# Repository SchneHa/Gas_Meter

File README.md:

# Gasverbrauch messen und verarbeiten 

## Funktion

Manche Gaszähler geben pro verbrauchte 10 Liter einen magnetischen Impuls ab.
Dieser Impuls wird mit einem Hall Sensor in elektrische Impulse umgewandelt, ein RTC Baustein PCF8583 arbeitet als Zähler und speichert die Zahl der Impulse im internen RAM ab.

PCB Eagle Dateien (für Version 1.3) und KiCAD Dateien (für Version 1.4) sowie Stückliste (BOM) für beide Versionen anbei.

Ich habe sowohl für die Version 1.3 als auch für die Version 1.4 noch einige Platinen übrig, bei Bedarf bitte melden:
```
PCB unbestückt: 5€
PCB mit Bauteilen: 15€
PCB fertig bestückt (ohne Knopfzelle und Hallsensor noch nicht bestückt): 20€
D1 mini ESP8266: 10€
inklusive Versand innerhalb Deutschlands
hans(dot)schneider(at)gmx(dot)ch
```

Die Daten werden mit Hilfe eines ESP8266 (z.B. Wemos D1 mini) über die I²C Schnittstelle ausgelesen und verarbeitet. 
Über das MQTT Protokoll werden die Daten an einen lokalen Broker weitergeleitet, Daten werden nicht ins Internet hochgeladen, es sei denn, man richtet die Verarbeitung über Thingspeak explizit ein.
Eine 3 Volt Knopfzelle versorgt den Baustein mit Energie und erhält die Daten bei Stromausfall. In der Version 1.4 wird der Sensor durch den ESP8266 versorgt, die Knopfzelle arbeitet als Backup Batterie.

* Diese Daten werden im RTC RAM gespeichert

1. Zählimpulse
2. Zählerstand zu Beginn der Messung (Counts=0)
3. Zählerstand zu Beginn der Abrechnungsperiode
4. monatlicher Verbrauch in m³
5. Datum und Uhrzeit des letzen Auslesens des RTC Bausteins

* Diese Daten werden über MQTT an den Broker gesendet

1. Uhrzeit 
2. Gesamtverbrauch in kWh
3. aktuelle Leistung in kW
4. Anzahl der Impulse seit Reset
5. Gesamtverbrauch in m³
6. Zählerstand zu Beginn der Messung (Counts=0) in Liter
7. Zählerstand zu Begin der Abrechnungsperiode in Liter
8. nach Bedarf monatlicher Verbrauch
9. Täglicher Verbrauch in l, kWh und m³
10. Status (OK wenn Zugriff auf den RTC Baustein möglich)

* Diese Daten/Kommandos können vom Broker an den ESP8266 gesendet werden

1. Veröffentliche den Verbrauch eines einzelnen Monats oder aller Monate von 1 to 12 
 * SYNTAX  : "Energy/Gas/command"
 * PAYLOAD : "Monat, x"
 * Wert für x: entweder 1 bis 12 für einen einzelnen Monat, oder x > 12 für alle 12 Monate
  
 2. Setze den Wert für den Verbrauch zu Beginn der Heizperiode 
 * SYNTAX  : "Energy/Gas/command"
 * PAYLOAD : "InitP, x"
 * Wert für x: Verbrauch in Litern

 3. Setze den initialen Verbrauchswert für den Counter Null 
 * SYNTAX  : "Energy/Gas/command"
 * PAYLOAD : "InitS, x"
 * Wert für x: Verbrauch in Litern

 4. Setze den initialen Wert für den Verbrauch eines einzelnen Monats  
 * SYNTAX  : "Energy/Gas/command"
 * PAYLOAD : "InitM, x ; y"
 * value for x: ausgewählter Monat
 * value for y: Verbrauch in Litern
 
 5. Setze den Wert für den Start der Abrechnungsperiode 
 * Initialisiert den RTC chip und setzt den initialen Verbrauchswert für count=0 der Abrechnungsperiode 
 * SYNTAX  : "Energy/Gas/command"
 * PAYLOAD : "InitC, x"
 * value for x: Verbrauch in Litern

 6. Setze den Tageszähler zurück auf Null 
 * Setzt den aktuellen Verbrauchswert für den Tageszähler auf 0 zurück 
 * SYNTAX  : "Energy/Gas/command"
 * PAYLOAD : "InitD"

## Vorbereitung

* in Gas_WiFi SSID und Passwort eintragen
* für ArduinoOTA (Firmware Update **O**ver **T**he **A**ir) hashed Wert eines gewählte Passortes eintragen, der Hash-Wert kann z.B. über https://hash-generieren.de/ oder https://www.md5hashgenerator.com/ oder https://www.hexhero.com/tools/sha256-hash-generator gebildet werden.    
* in Gas_MQTT IP Adresse des MQTT Broker eintragen
* ggfs. Thingspeak aktivieren und Channelnummer und Key eintragen
* Topic für MQTT an die eigenen Wünsche anpassen

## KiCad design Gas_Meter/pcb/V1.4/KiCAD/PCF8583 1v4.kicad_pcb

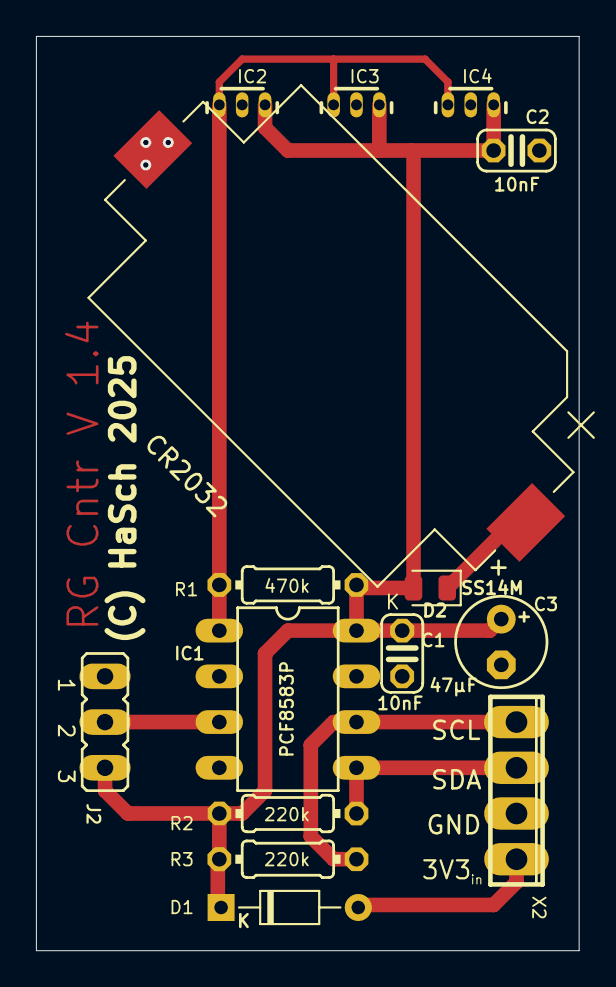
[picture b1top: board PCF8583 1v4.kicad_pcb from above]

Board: 2 copper layers, 30.2 x 50.8 mm, 15 parts (0 on the bottom side), 7 nets.

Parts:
C1, C2: 10nF; C025-024X044
C3: 47µF; E2,5-5
CR2032: BatteryHolder_Keystone_1060_1x2032
D1: 1N4148; D_DO-34_SOD68_P7.62mm_Horizontal
D2: SS14M; D_0805_2012Metric
IC1: PCF8583P; DIL08
IC2, IC3, IC4: A1301UA; SIP3-UA
J2: JP2
R1: 470k; 0204_7
R2, R3: 220k; 0204_7
X2: 4POL254

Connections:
CNT: IC1.1, IC2.3, IC3.3, IC4.3, R1.1
GND: C1.2, C2.2, C3.-, CR2032.2, IC1.4, IC2.2, IC3.2, IC4.2, J2.1, X2.3
unnamed: D1.2, X2.4
unnamed: IC1.3, J2.2
SCL: IC1.6, R3.1, X2.1
SDA: IC1.5, R2.1, X2.2
VDD: C1.1, C2.1, C3.+, D1.1, D2.2, IC1.8, IC2.1, IC3.1, IC4.1, J2.3, R1.2, R2.2, R3.2

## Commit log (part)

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2025-07-12 Update README.md
    corrections
2025-07-12 Update Gas_Counter_CP.ino
    corrections
2025-07-12 Update Gas_Counter_CP.txt
    corrections
2025-07-16 Update README.md
    Adjustments for V1.4
2025-07-28 Create Gaszähler Dokumentation Langversion V1.4.pdf
    Updated "Langversion" to V1.4
2025-08-04 README.md aktualisieren
2026-06-10 Fix typos and enhance MQTT data processing explanation
    Corrected spelling mistakes and clarified data processing details regarding MQTT and Thingspeak.
2026-06-10 OTA added, Daily Counts added, Monthly values corrected
2026-06-10 deleting previous version
2026-06-10 Update print statement from 'Hello' to 'Goodbye'
2026-06-10 Update WiFi connection code with placeholder values
2026-06-10 Update ThingSpeak credentials and channel number
2026-06-10 Update fmt.Println output from 'Hello' to 'Goodbye'
2026-06-10 Update README with revised consumption metrics
2026-06-10 Update README with ArduinoOTA instructions
    Added instructions for ArduinoOTA hashed value in README.
2026-06-10 Refactor MQTT setup and publish functions
2026-06-10 Fix formatting in README for ArduinoOTA section
2026-06-23 Update Gaszaehler_CP.ino
    At the start of the new billing period, an old initial consumption value is no longer carried over.
2026-06-26 The day counter is now resettable. Comment lines have been added to improve code readability.
2026-06-26 Updating documentation
2026-06-26 Updating firmware
2026-06-26 Update README with daily counter reset instructions
    Added instructions for resetting the daily counter and updated links for hash generation.
2026-06-26 More nescommented li
2026-06-26 More commented lines
2026-06-27 Next attempt to make the day change more stable in conjunction with InitD.
2026-06-27 Uddating firmware
2026-06-27 Next attempt to improve the day counter
2026-06-27 Improvement of detecting the deep sleep mode block (D6 connected to GND)
2026-06-27 Improvement of deep sleep mode block detection
2026-06-29 Now (hopefully) the last bug has been fixed.
2026-06-29 Firmware updated
2026-06-29 More comments
2026-06-30 final compact DS1307 RAM layout
